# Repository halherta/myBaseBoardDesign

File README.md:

# Baseboard for the IOT innovation Station (IOTIS)

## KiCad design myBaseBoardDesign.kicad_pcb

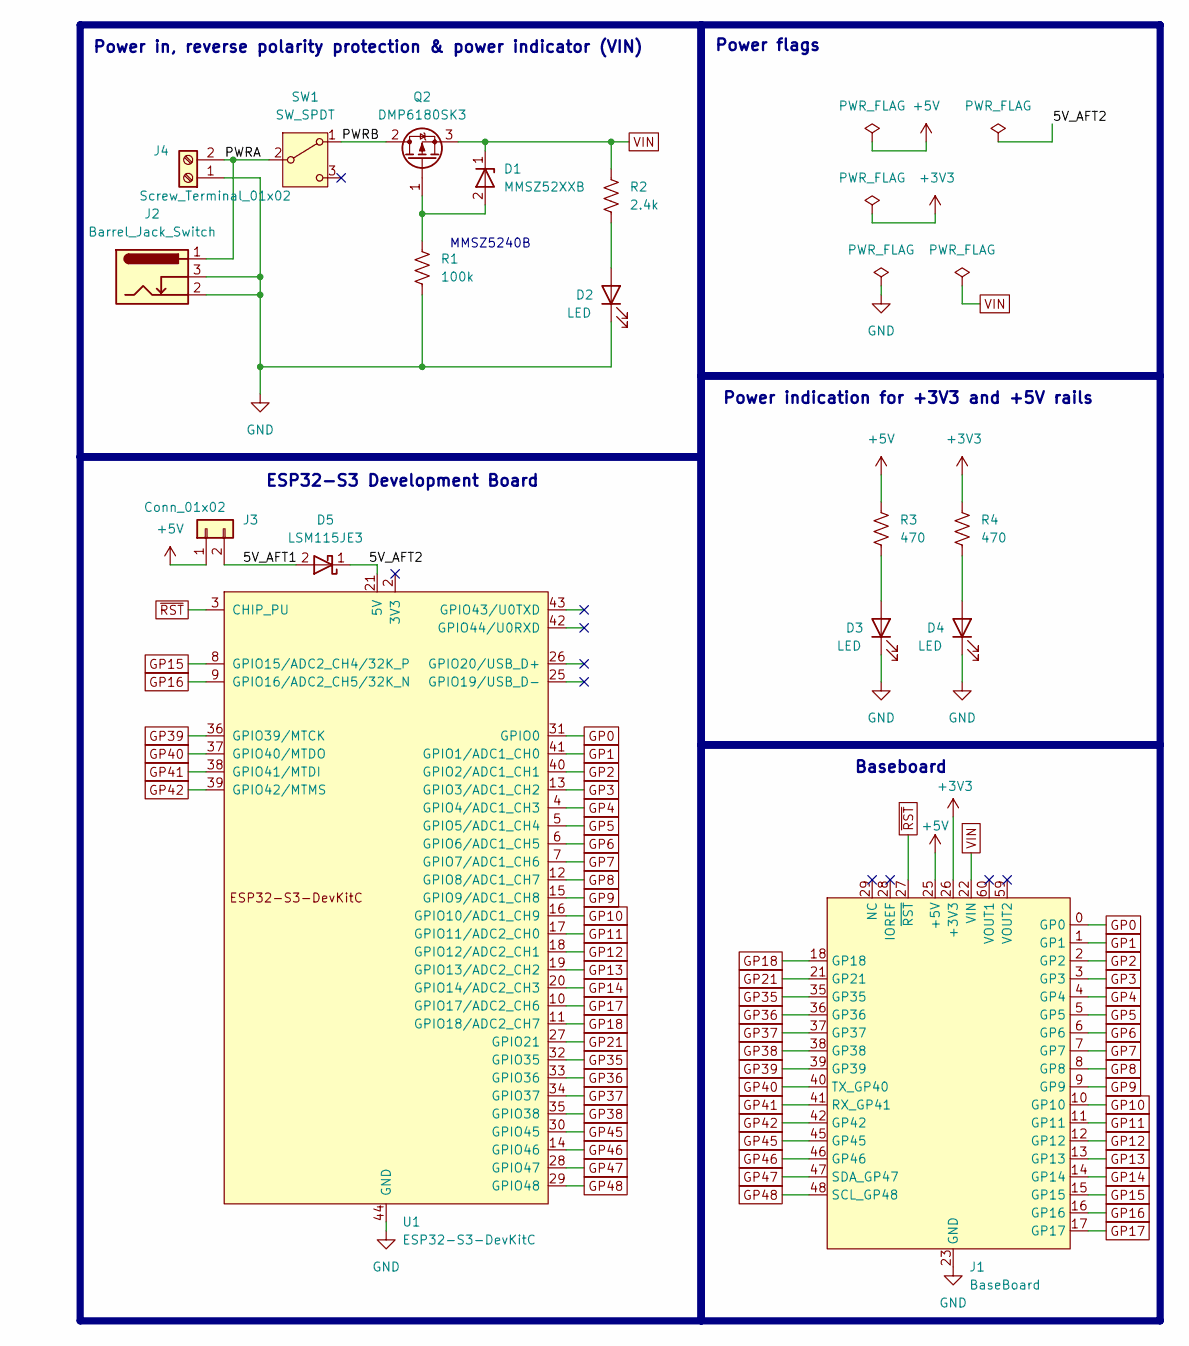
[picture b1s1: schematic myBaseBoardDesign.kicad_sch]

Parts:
D1: MMSZ52XXB; D_SOD-123
D2, D3, D4: LED; LED_1206_3216Metric_Pad1.42x1.75mm_HandSolder
D5: LSM115JE3; D_SMA
J1: BaseBoard; BaseBoardTemplate
J2: Barrel_Jack_Switch; BarrelJack_CUI_PJ-102AH_Horizontal
J3: Conn_01x02; PinHeader_1x02_P2.54mm_Vertical
J4: Screw_Terminal_01x02; TerminalBlock_Altech_AK300-2_P5.00mm
Q2: DMP6180SK3; TO-252-2
R1: 100k; R_1206_3216Metric_Pad1.30x1.75mm_HandSolder
R2: 2.4k; R_1206_3216Metric_Pad1.30x1.75mm_HandSolder
R3, R4: 470; R_1206_3216Metric_Pad1.30x1.75mm_HandSolder
SW1: SW_SPDT; SW_E-Switch_EG1224_SPDT_Angled
U1: ESP32-S3-DevKitC

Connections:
+3V3: J1.26 (+3V3), J1.32 (+3V3), J1.62 (+3V3), R4.1
+5V: J1.25 (+5V), J1.61 (+5V), J3.1, R3.1
/5V_AFT1: D5.2 (A), J3.2
/5V_AFT2: D5.1 (K), U1.21 (5V)
/PWRA: J2.1, J4.2, SW1.2 (B)
/PWRB: Q2.2 (D), SW1.1 (A)
GND: D2.1 (K), D3.1 (K), D4.1 (K), J1.23 (GND), J1.24 (GND), J1.30 (GND), J1.55 (GND), J1.56 (GND), J1.57 (GND), J1.58 (GND), J2.2, J2.3, J4.1, R1.2, U1.22 (GND), U1.23 (GND), U1.24 (GND), U1.44 (GND)
GP0: J1.0 (GP0), U1.31 (GPIO0)
GP1: J1.1 (GP1), U1.41 (GPIO1/ADC1_CH0)
GP2: J1.2 (GP2), U1.40 (GPIO2/ADC1_CH1)
GP3: J1.3 (GP3), U1.13 (GPIO3/ADC1_CH2)
GP4: J1.4 (GP4), U1.4 (GPIO4/ADC1_CH3)
GP5: J1.5 (GP5), U1.5 (GPIO5/ADC1_CH4)
GP6: J1.6 (GP6), U1.6 (GPIO6/ADC1_CH5)
GP7: J1.7 (GP7), U1.7 (GPIO7/ADC1_CH6)
GP8: J1.8 (GP8), U1.12 (GPIO8/ADC1_CH7)
GP9: J1.9 (GP9), U1.15 (GPIO9/ADC1_CH8)
GP10: J1.10 (GP10), U1.16 (GPIO10/ADC1_CH9)
GP11: J1.11 (GP11), U1.17 (GPIO11/ADC2_CH0)
GP12: J1.12 (GP12), U1.18 (GPIO12/ADC2_CH1)
GP13: J1.13 (GP13), U1.19 (GPIO13/ADC2_CH2)
GP14: J1.14 (GP14), U1.20 (GPIO14/ADC2_CH3)
GP15: J1.15 (GP15), U1.8 (GPIO15/ADC2_CH4/32K_P)
GP16: J1.16 (GP16), U1.9 (GPIO16/ADC2_CH5/32K_N)
GP17: J1.17 (GP17), U1.10 (GPIO17/ADC2_CH6)
GP18: J1.18 (GP18), U1.11 (GPIO18/ADC2_CH7)
GP21: J1.21 (GP21), U1.27 (GPIO21)
GP35: J1.35 (GP35), U1.32 (GPIO35)
GP36: J1.36 (GP36), U1.33 (GPIO36)
GP37: J1.37 (GP37), U1.34 (GPIO37)
GP38: J1.38 (GP38), U1.35 (GPIO38)
GP39: J1.39 (GP39), U1.36 (GPIO39/MTCK)
GP40: J1.40 (TX_GP40), U1.37 (GPIO40/MTDO)
GP41: J1.41 (RX_GP41), U1.38 (GPIO41/MTDI)
GP42: J1.42 (GP42), U1.39 (GPIO42/MTMS)
GP45: J1.45 (GP45), U1.30 (GPIO45)
GP46: J1.46 (GP46), U1.14 (GPIO46)
GP47: J1.47 (SDA_GP47), U1.28 (GPIO47)
GP48: J1.48 (SCL_GP48), U1.29 (GPIO48)
unnamed: D1.2 (A), Q2.1 (G), R1.1
unnamed: D2.2 (A), R2.2
unnamed: D3.2 (A), R3.2
unnamed: D4.2 (A), R4.2
VIN: D1.1 (K), J1.22 (VIN), J1.53 (VIN), J1.54 (VIN), Q2.3 (S), R2.1
~RST: J1.27 (~RST), U1.3 (CHIP_PU)

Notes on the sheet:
ESP32-S3 Development Board
MMSZ5240B
Power flags
Power in, reverse polarity protection & power indicator (VIN)
Baseboard
Power indication for +3V3 and +5V rails

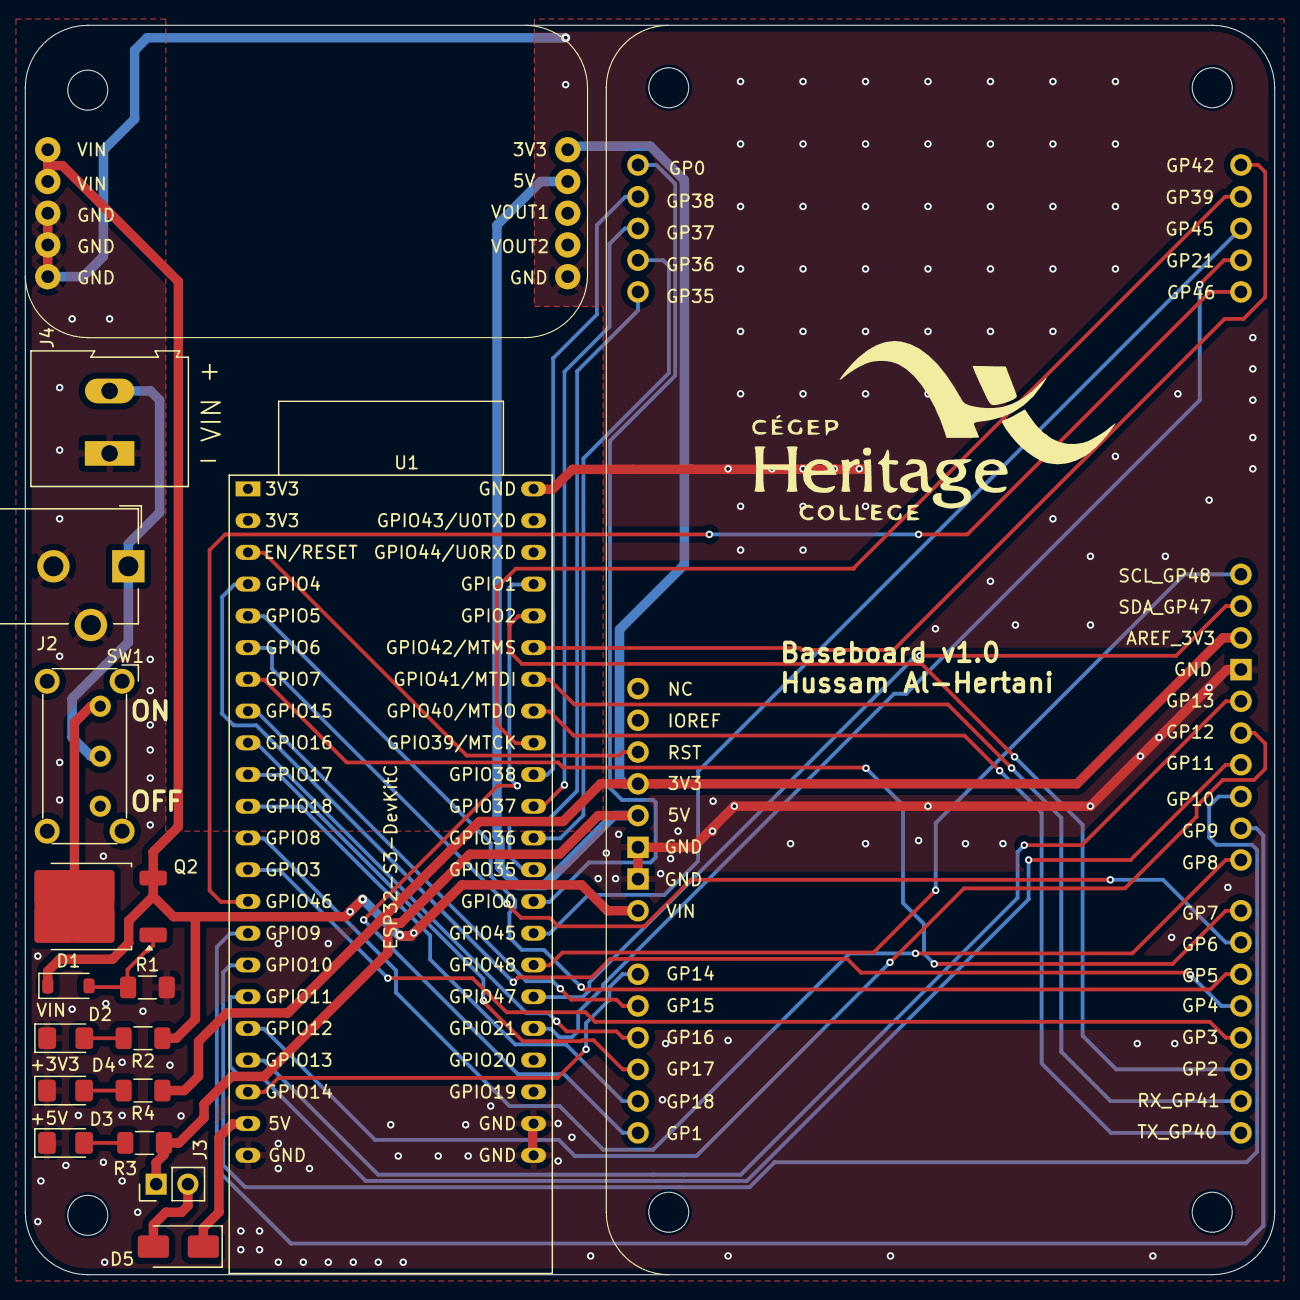
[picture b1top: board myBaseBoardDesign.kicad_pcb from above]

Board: 2 copper layers, 100.0 x 100.0 mm, 16 parts (0 on the bottom side), 45 nets.
